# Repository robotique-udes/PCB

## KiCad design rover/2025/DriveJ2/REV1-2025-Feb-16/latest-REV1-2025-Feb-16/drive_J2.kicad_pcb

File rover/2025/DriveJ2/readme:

REV0 - C'est le first draft un peu gros, mais normalement tout est chill

hopefully j'ai le temps de le shrinker un peu avant la commande avec la rev1

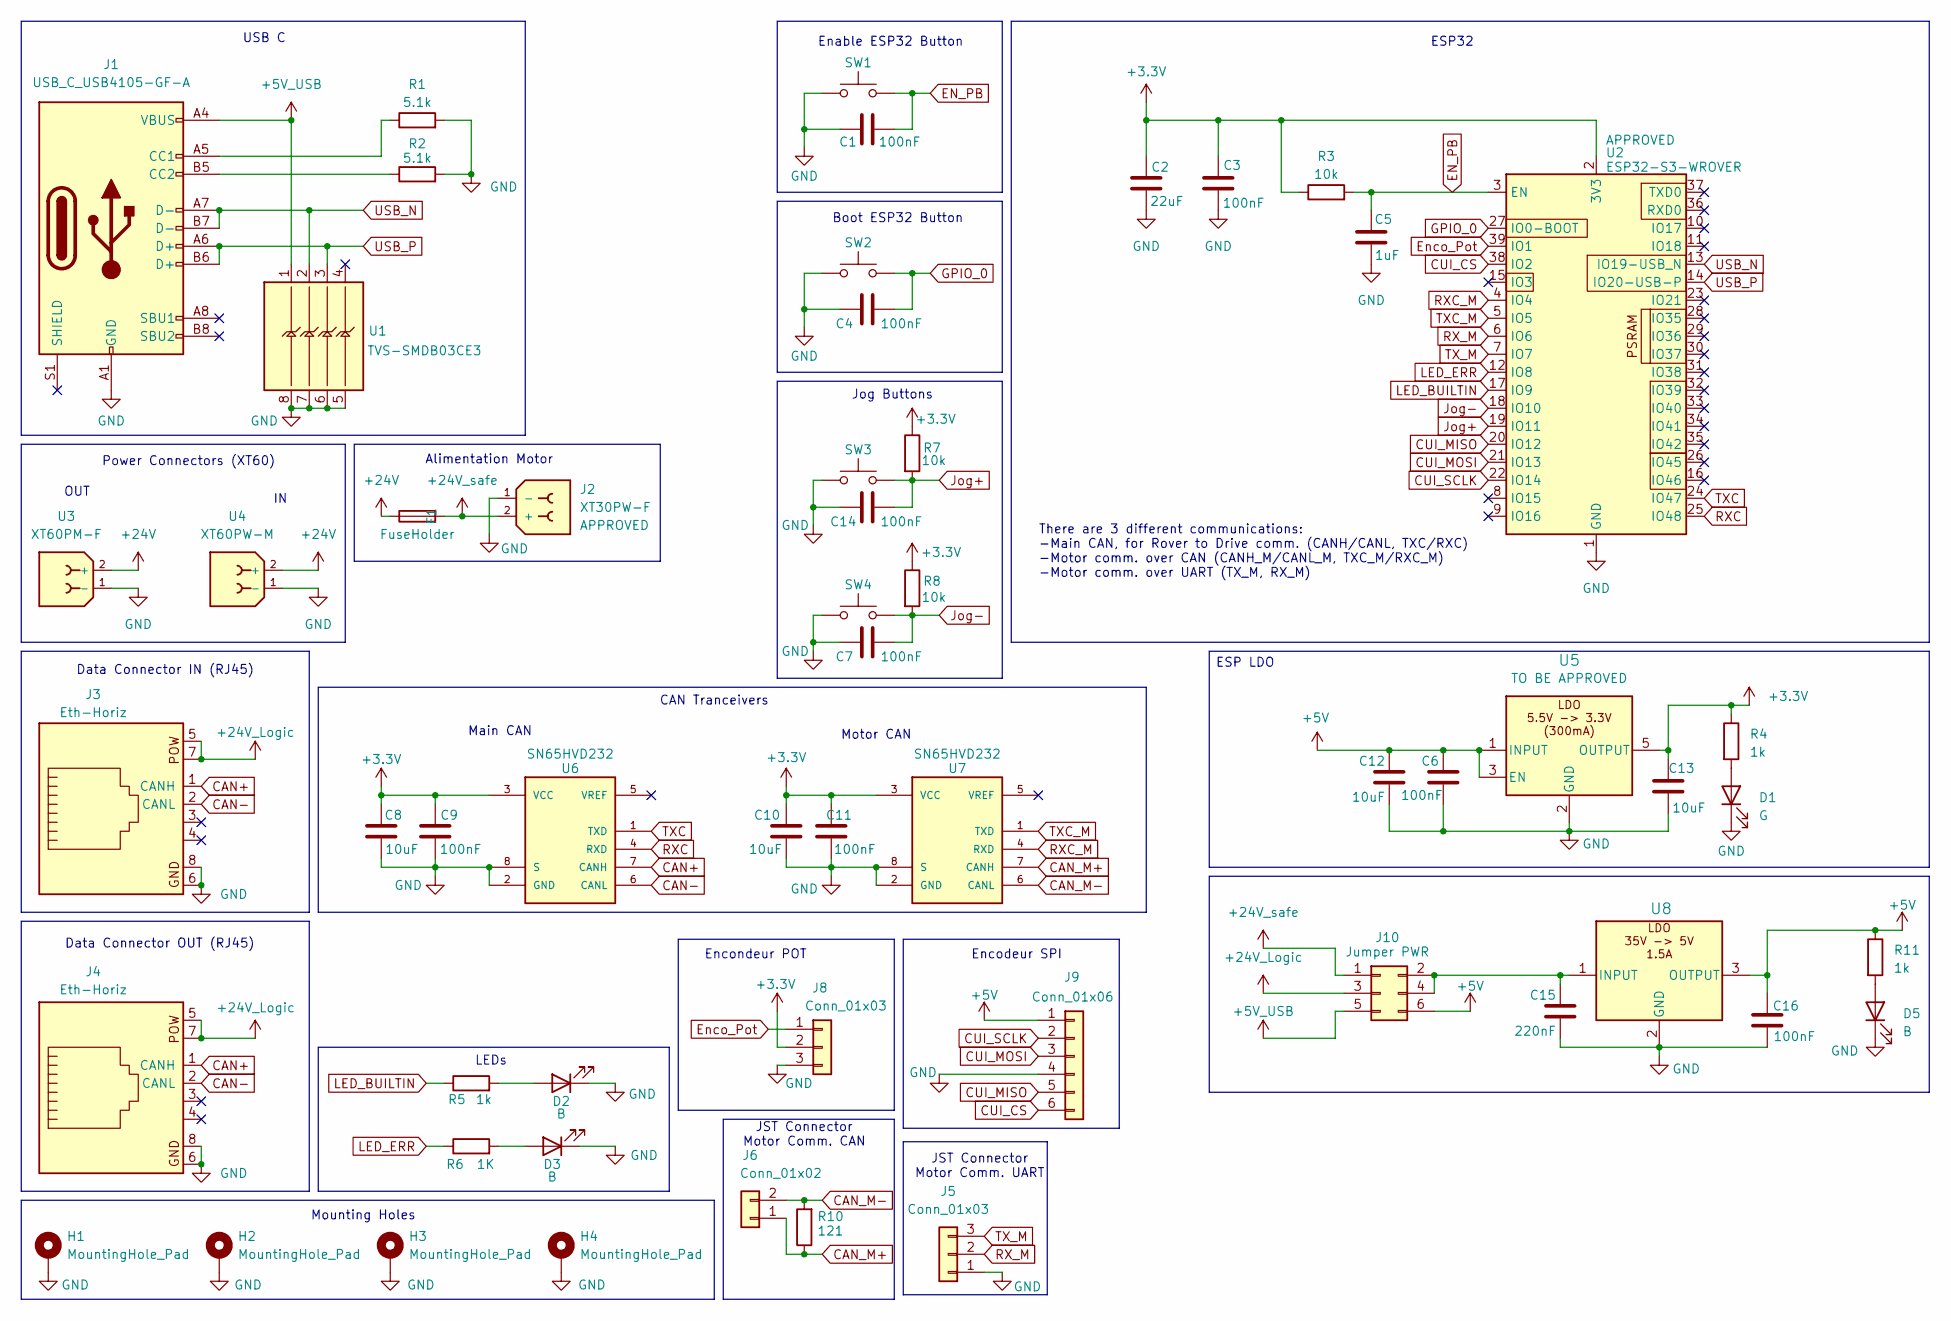
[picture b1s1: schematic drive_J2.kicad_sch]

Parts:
C1, C3, C4, C6, C7, C9, C11, C14, C16: 100nF; C_0805_2012Metric_Pad1.18x1.45mm_HandSolder
C2: 22uF; C_0805_2012Metric_Pad1.18x1.45mm_HandSolder
C5: 1uF; C_0805_2012Metric_Pad1.18x1.45mm_HandSolder
C8, C10, C12, C13: 10uF; C_0805_2012Metric_Pad1.18x1.45mm_HandSolder
C15: 220nF; C_0805_2012Metric_Pad1.18x1.45mm_HandSolder
D1: G; LED_0805_2012Metric_Pad1.15x1.40mm_HandSolder
D2, D3, D5: B; LED_0805_2012Metric_Pad1.15x1.40mm_HandSolder
F1: FuseHolder; FUSE_3568-20
H1, H2, H3, H4: MountingHole_Pad; MountingHole_3.2mm_M3_DIN965_Pad_TopBottom
J1: USB_C_USB4105-GF-A; USB_C_Receptacle_GCT_USB4105-xx-A_16P_TopMnt_Horizontal
J2: XT30PW-F; AMASS_XT30PW-F_1x02_P2.50mm_Horizontal; PARTREV 1.2
J3, J4: Eth-Horiz; Ethernet_Horizontal
J5: Conn_01x03; JST_PH_S3B-PH-K_1x03_P2.00mm_Horizontal
J6: Conn_01x02; JST_PH_S2B-PH-K_1x02_P2.00mm_Horizontal
J8: Conn_01x03; JST_PH_B3B-PH-K_1x03_P2.00mm_Vertical
J9: Conn_01x06; JST_PH_B6B-PH-K_1x06_P2.00mm_Vertical
J10: Jumper PWR; PinHeader_2x03_P2.54mm_Vertical
R1, R2: 5.1k; R_0805_2012Metric_Pad1.20x1.40mm_HandSolder
R3, R7, R8: 10k; R_0805_2012Metric_Pad1.20x1.40mm_HandSolder
R4, R5, R11: 1k; R_0805_2012Metric_Pad1.20x1.40mm_HandSolder
R6: 1K; R_0805_2012Metric_Pad1.20x1.40mm_HandSolder
R10: 121; R_0805_2012Metric_Pad1.20x1.40mm_HandSolder
SW1, SW2, SW3, SW4: SW-PTS815SJM250SMTRLFS; SW-PTS815 SJM250SMTRLFS
U1: TVS-SMDB03CE3; SOIC-8_3.9x4.9mm_P1.27mm
U2: ESP32-S3-WROVER; ESP32-S3-WROOM-1U
U3: XT60PM-F; AMASS_XT60PW-F_1x02_P7.20mm_Horizontal
U4: XT60PW-M; AMASS_XT60PW-M_1x02_P7.20mm_Horizontal
U5: LDO-TLV74033PDBVR; SOT-23-5_HandSoldering
U6, U7: SN65HVD232; SOIC-8_3.9x4.9mm_P1.27mm; PARTREV 4
U8: LDO-LM7805MPX/NOPB; SOT-223-3_TabPin2

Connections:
+3.3V: C2.1, C3.1, C8.1, C9.1, C10.1, C11.1, C13.1, J8.2, R3.1, R4.1, R7.1, R8.1, U2.2 (3V3), U5.5 (OUTPUT), U6.3 (VCC), U7.3 (VCC)
+5V: C6.1, C12.1, C16.1, J9.1, J10.6, R11.1, U5.1 (INPUT), U5.3 (EN), U8.3 (OUTPUT)
+5V_USB: J1.A4 (VBUS), J1.A9 (VBUS), J1.B4 (VBUS), J1.B9 (VBUS), J10.5, U1.1
+24V: F1.2, U3.2 (+), U4.2 (+)
+24V_Logic: J3.5, J3.7, J4.5, J4.7, J10.3
+24V_safe: F1.1, J2.2 (+), J10.1
CAN+: J3.1 (CANH), J4.1 (CANH), U6.7 (CANH)
CAN-: J3.2 (CANL), J4.2 (CANL), U6.6 (CANL)
CAN_M+: J6.1, R10.1, U7.7 (CANH)
CAN_M-: J6.2, R10.2, U7.6 (CANL)
CUI_CS: J9.6, U2.38 (IO2)
CUI_MISO: J9.5, U2.20 (IO12)
CUI_MOSI: J9.3, U2.21 (IO13)
CUI_SCLK: J9.2, U2.22 (IO14)
EN_PB: C1.2, C5.1, R3.2, SW1.4, U2.3 (EN)
Enco_Pot: J8.1, U2.39 (IO1)
GND: C1.1, C2.2, C3.2, C4.1, C5.2, C6.2, C7.1, C8.2, C9.2, C10.2, C11.2, C12.2, C13.2, C14.1, C15.2, C16.2, D1.1 (K), D2.1 (K), D3.1 (K), D5.1 (K), H1.1, H2.1, H3.1, H4.1, J1.A1 (GND), J1.A12 (GND), J1.B1 (GND), J1.B12 (GND), J2.1 (-), J3.6, J3.8, J4.6, J4.8, J5.1, J8.3, J9.4, R1.2, R2.2, SW1.1, SW1.2, SW2.1, SW2.2, SW3.1, SW3.2, SW4.1, SW4.2, U1.5, U1.6, U1.7, U1.8, U2.1 (GND), U2.40 (GND), U2.41 (GND), U3.1 (-), U4.1 (-), U5.2 (GND), U6.2 (GND), U6.8 (S), U7.2 (GND), U7.8 (S), U8.2 (GND)
GPIO_0: C4.2, SW2.4, U2.27 (IO0-BOOT)
Jog+: C14.2, R7.2, SW3.4, U2.19 (IO11)
Jog-: C7.2, R8.2, SW4.4, U2.18 (IO10)
LED_BUILTIN: R5.1, U2.17 (IO9)
LED_ERR: R6.1, U2.12 (IO8)
unnamed: D1.2 (A), R4.2
unnamed: D2.2 (A), R5.2
unnamed: D3.2 (A), R6.2
unnamed: D5.2 (A), R11.2
unnamed: J1.A5 (CC1), R1.1
unnamed: J1.B5 (CC2), R2.1
unnamed: C15.1, J10.2, J10.4, U8.1 (INPUT)
RXC: U2.25 (IO48), U6.4 (RXD)
RXC_M: U2.4 (IO4), U7.4 (RXD)
RX_M: J5.2, U2.6 (IO6)
TXC: U2.24 (IO47), U6.1 (TXD)
TXC_M: U2.5 (IO5), U7.1 (TXD)
TX_M: J5.3, U2.7 (IO7)
USB_N: J1.A7 (D-), J1.B7 (D-), U1.2, U2.13 (IO19-USB_N)
USB_P: J1.A6 (D+), J1.B6 (D+), U1.3, U2.14 (IO20-USB-P)

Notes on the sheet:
ESP32
Data Connector IN (RJ45)
OUT
Mounting Holes
Encodeur SPI
Power Connectors (XT60)
JST Connector Motor Comm. UART
Main CAN
Motor CAN
There are 3 different communications: -Main CAN, for Rover to Drive comm. (CANH/CANL, TXC/RXC) -Motor comm. over CAN (CANH_M/CANL_M, TXC_M/RXC_M) -Motor comm. over UART (TX_M, RX_M)
ESP LDO
Alimentation Motor
Boot ESP32 Button
Jog Buttons
Enable ESP32 Button
CAN Tranceivers
Data Connector OUT (RJ45)
USB C
LEDs
Encondeur POT
JST Connector Motor Comm. CAN

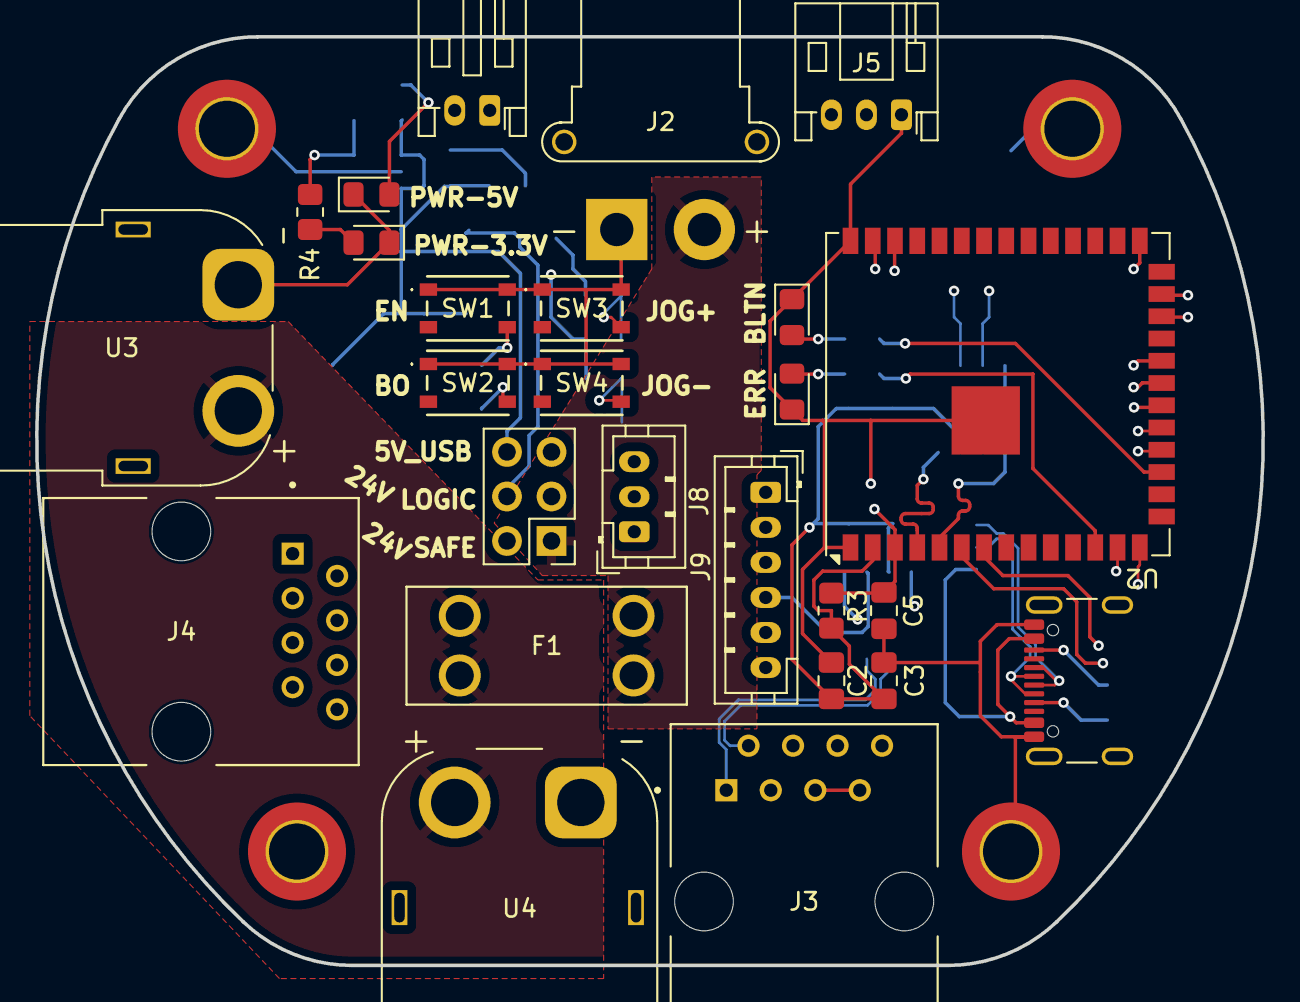
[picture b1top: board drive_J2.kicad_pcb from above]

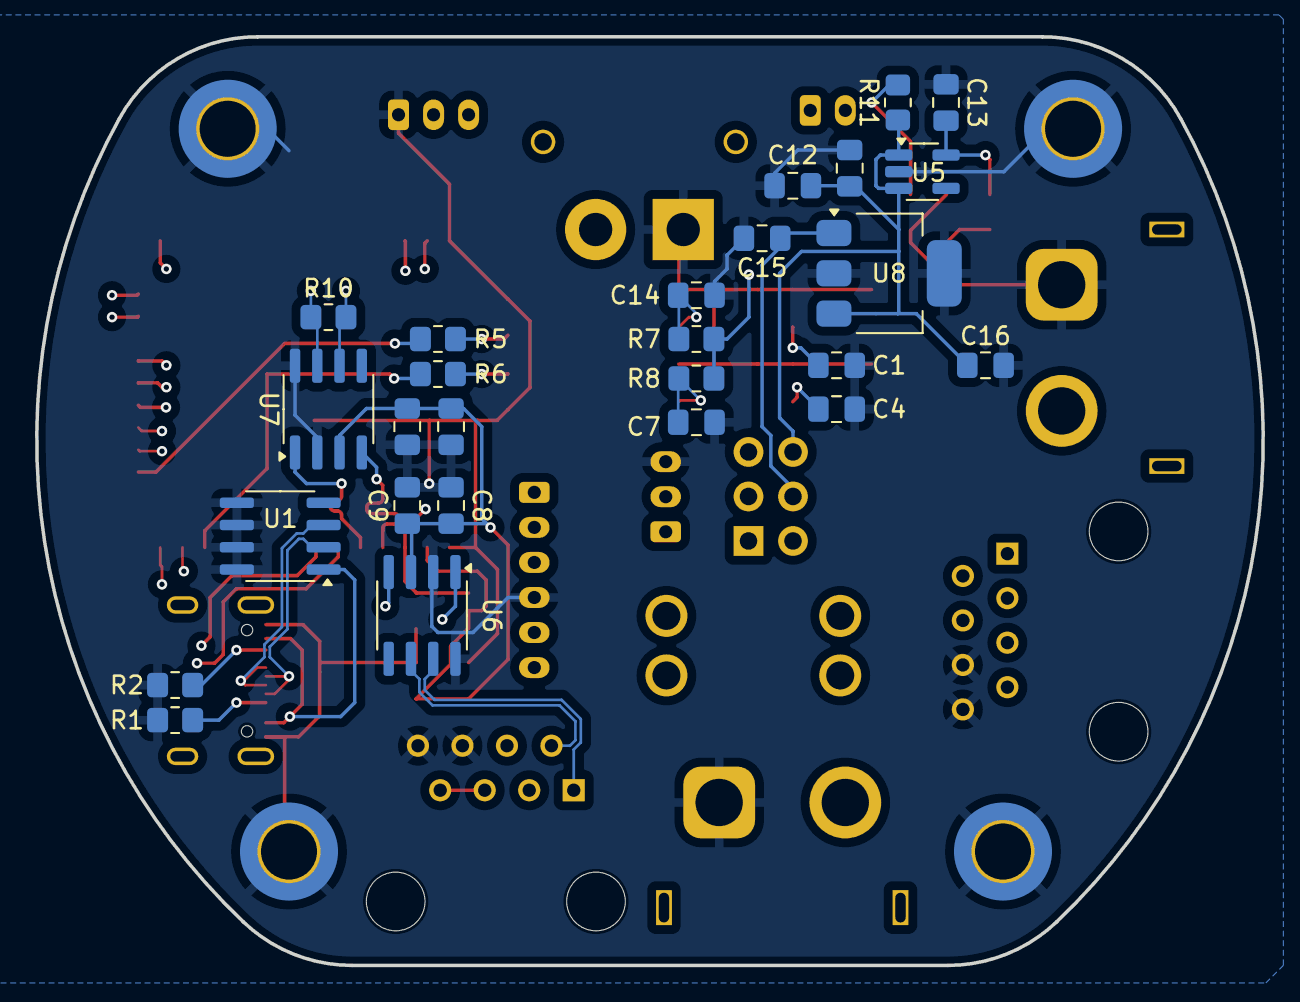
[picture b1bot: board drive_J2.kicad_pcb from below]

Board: 4 copper layers, 70.0 x 53.0 mm, 56 parts (26 on the bottom side), 37 nets.

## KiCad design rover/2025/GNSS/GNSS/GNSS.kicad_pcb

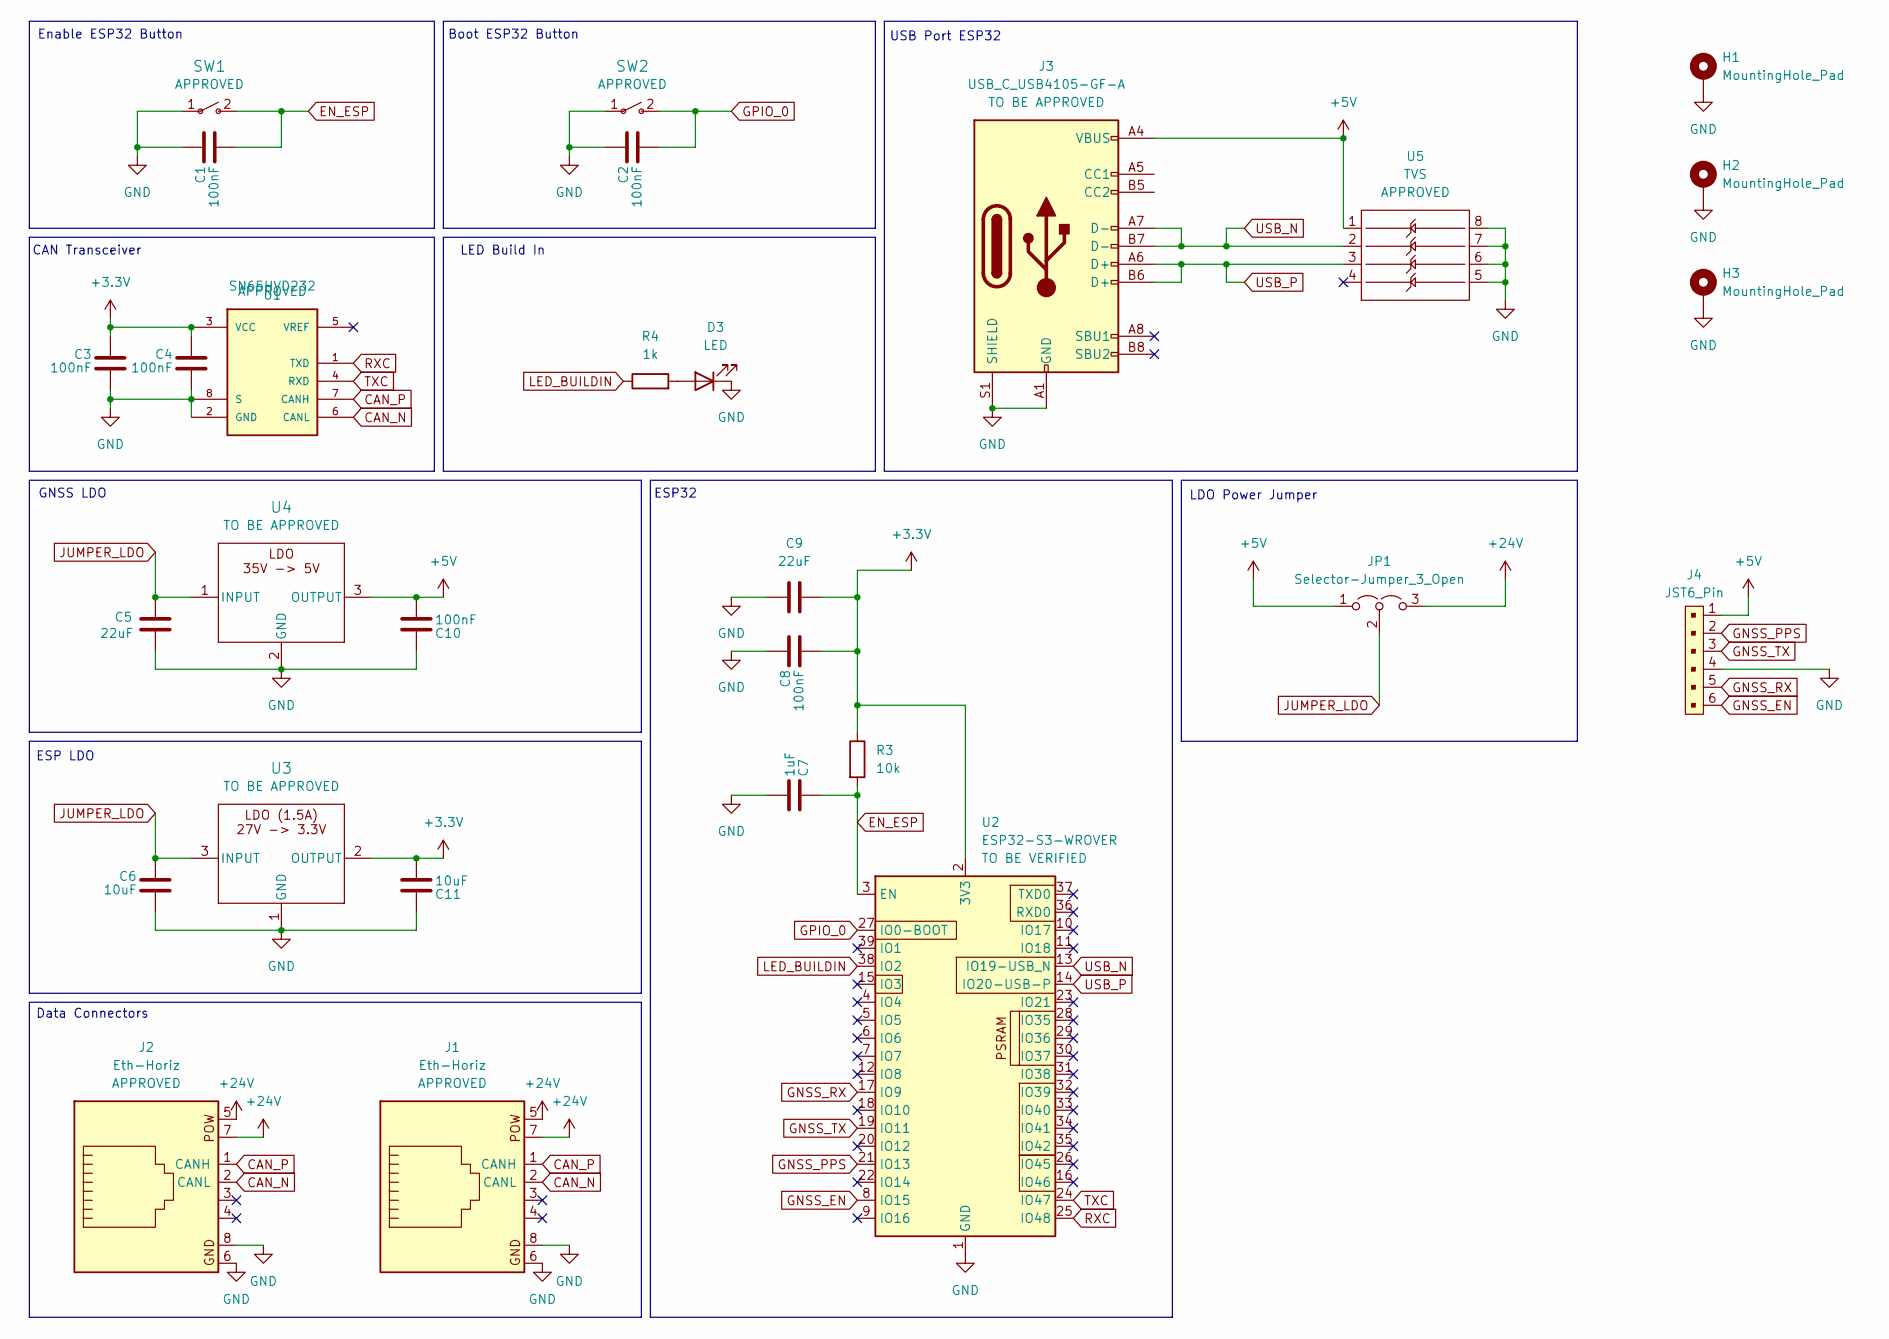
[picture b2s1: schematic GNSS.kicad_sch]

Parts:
C1, C2, C3, C4, C8, C10: 100nF; C_0805_2012Metric_Pad1.18x1.45mm_HandSolder
C5, C9: 22uF; C_0805_2012Metric_Pad1.18x1.45mm_HandSolder
C6, C11: 10uF; C_0805_2012Metric_Pad1.18x1.45mm_HandSolder
C7: 1uF; C_0805_2012Metric_Pad1.18x1.45mm_HandSolder
D3: LED; LED_0805_2012Metric_Pad1.15x1.40mm_HandSolder
H1, H2, H3: MountingHole_Pad; MountingHole_3.2mm_M3_DIN965_Pad_TopBottom
J1, J2: Eth-Horiz; Ethernet_Horizontal
J3: USB_C_USB4105-GF-A; USB_C_Receptacle_GCT_USB4105-xx-A_16P_TopMnt_Horizontal
J4: JST6_Pin; JST_XH_B6B-XH-AM_1x06_P2.50mm_Vertical
JP1: Selector-Jumper_3_Open; PinHeader_1x03_P2.54mm_Vertical
R3: 10k; R_0805_2012Metric_Pad1.20x1.40mm_HandSolder
R4: 1k; R_0805_2012Metric_Pad1.20x1.40mm_HandSolder
SW1, SW2: TS09-63-25-WT-160-SMT-TR; SW_DIP_SPSTx01_Slide_6.7x4.1mm_W8.61mm_P2.54mm_LowProfile
U1: SN65HVD232; SOIC-8_3.9x4.9mm_P1.27mm; PARTREV 4
U2: ESP32-S3-WROVER; ESP32-S3-WROOM-1U
U3: LD1086DT33TR; TO-252-2
U4: LDO-LM7805MPX/NOPB; SOT-223-3_TabPin2
U5: TVS; SOIC-8_3.9x4.9mm_P1.27mm

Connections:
+3.3V: C3.1, C4.1, C8.2, C9.2, C11.2, R3.1, U1.3 (VCC), U2.2 (3V3), U3.2 (OUTPUT)
+5V: C10.2, J3.A4 (VBUS), J3.A9 (VBUS), J3.B4 (VBUS), J3.B9 (VBUS), J4.1, JP1.1 (A), U4.3 (OUTPUT), U5.1
+24V: J1.5, J1.7, J2.5, J2.7, JP1.3 (B)
CAN_N: J1.2 (CANL), J2.2 (CANL), U1.6 (CANL)
CAN_P: J1.1 (CANH), J2.1 (CANH), U1.7 (CANH)
EN_ESP: C1.2, C7.1, R3.2, SW1.2, U2.3 (EN)
GND: C1.1, C2.1, C3.2, C4.2, C5.1, C6.2, C7.2, C8.1, C9.1, C10.1, C11.1, D3.1 (K), H1.1, H2.1, H3.1, J1.6, J1.8, J2.6, J2.8, J3.A1 (GND), J3.A12 (GND), J3.B1 (GND), J3.B12 (GND), J3.S1 (SHIELD), J4.4, SW1.1, SW2.1, U1.2 (GND), U1.8 (S), U2.1 (GND), U2.40 (GND), U2.41 (GND), U3.1 (GND), U4.2 (GND), U5.5, U5.6, U5.7, U5.8
GNSS_EN: J4.6, U2.8 (IO15)
GNSS_PPS: J4.2, U2.21 (IO13)
GNSS_RX: J4.5, U2.17 (IO9)
GNSS_TX: J4.3, U2.19 (IO11)
GPIO_0: C2.2, SW2.2, U2.27 (IO0-BOOT)
JUMPER_LDO: C5.2, C6.1, JP1.2 (C), U3.3 (INPUT), U4.1 (INPUT)
LED_BUILDIN: R4.1, U2.38 (IO2)
unnamed: D3.2 (A), R4.2
RXC: U1.1 (TXD), U2.25 (IO48)
TXC: U1.4 (RXD), U2.24 (IO47)
USB_N: J3.A7 (D-), J3.B7 (D-), U2.13 (IO19-USB_N), U5.2
USB_P: J3.A6 (D+), J3.B6 (D+), U2.14 (IO20-USB-P), U5.3

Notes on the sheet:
Enable ESP32 Button
Data Connectors
Boot ESP32 Button
LED Build In
ESP32
CAN Transceiver
ESP LDO
GNSS LDO
LDO Power Jumper
USB Port ESP32

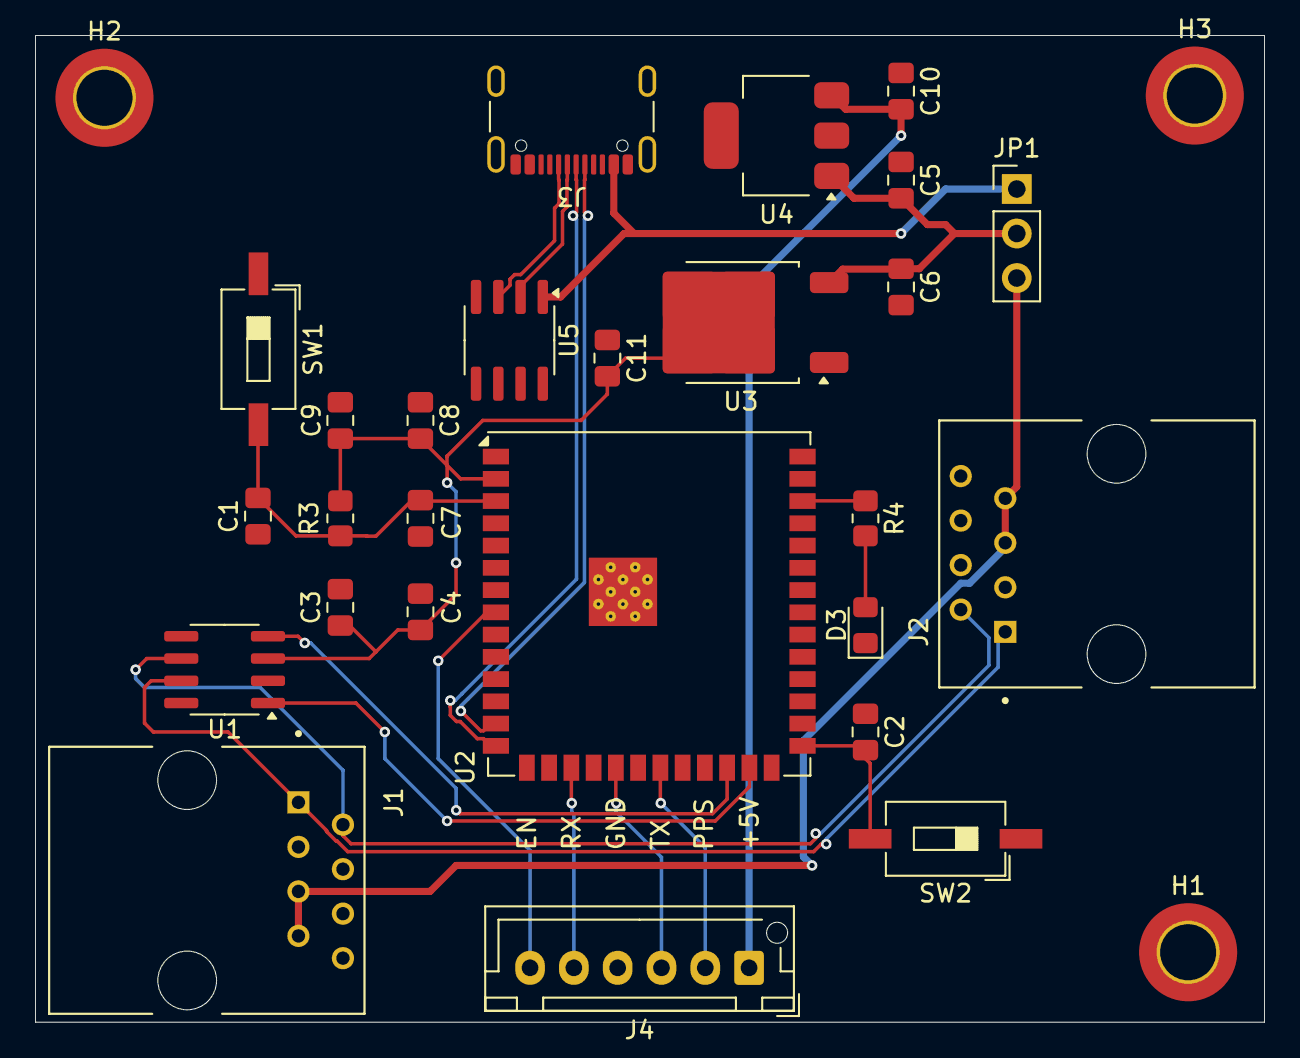
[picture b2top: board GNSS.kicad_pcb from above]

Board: 2 copper layers, 70.1 x 56.3 mm, 29 parts (0 on the bottom side), 19 nets.

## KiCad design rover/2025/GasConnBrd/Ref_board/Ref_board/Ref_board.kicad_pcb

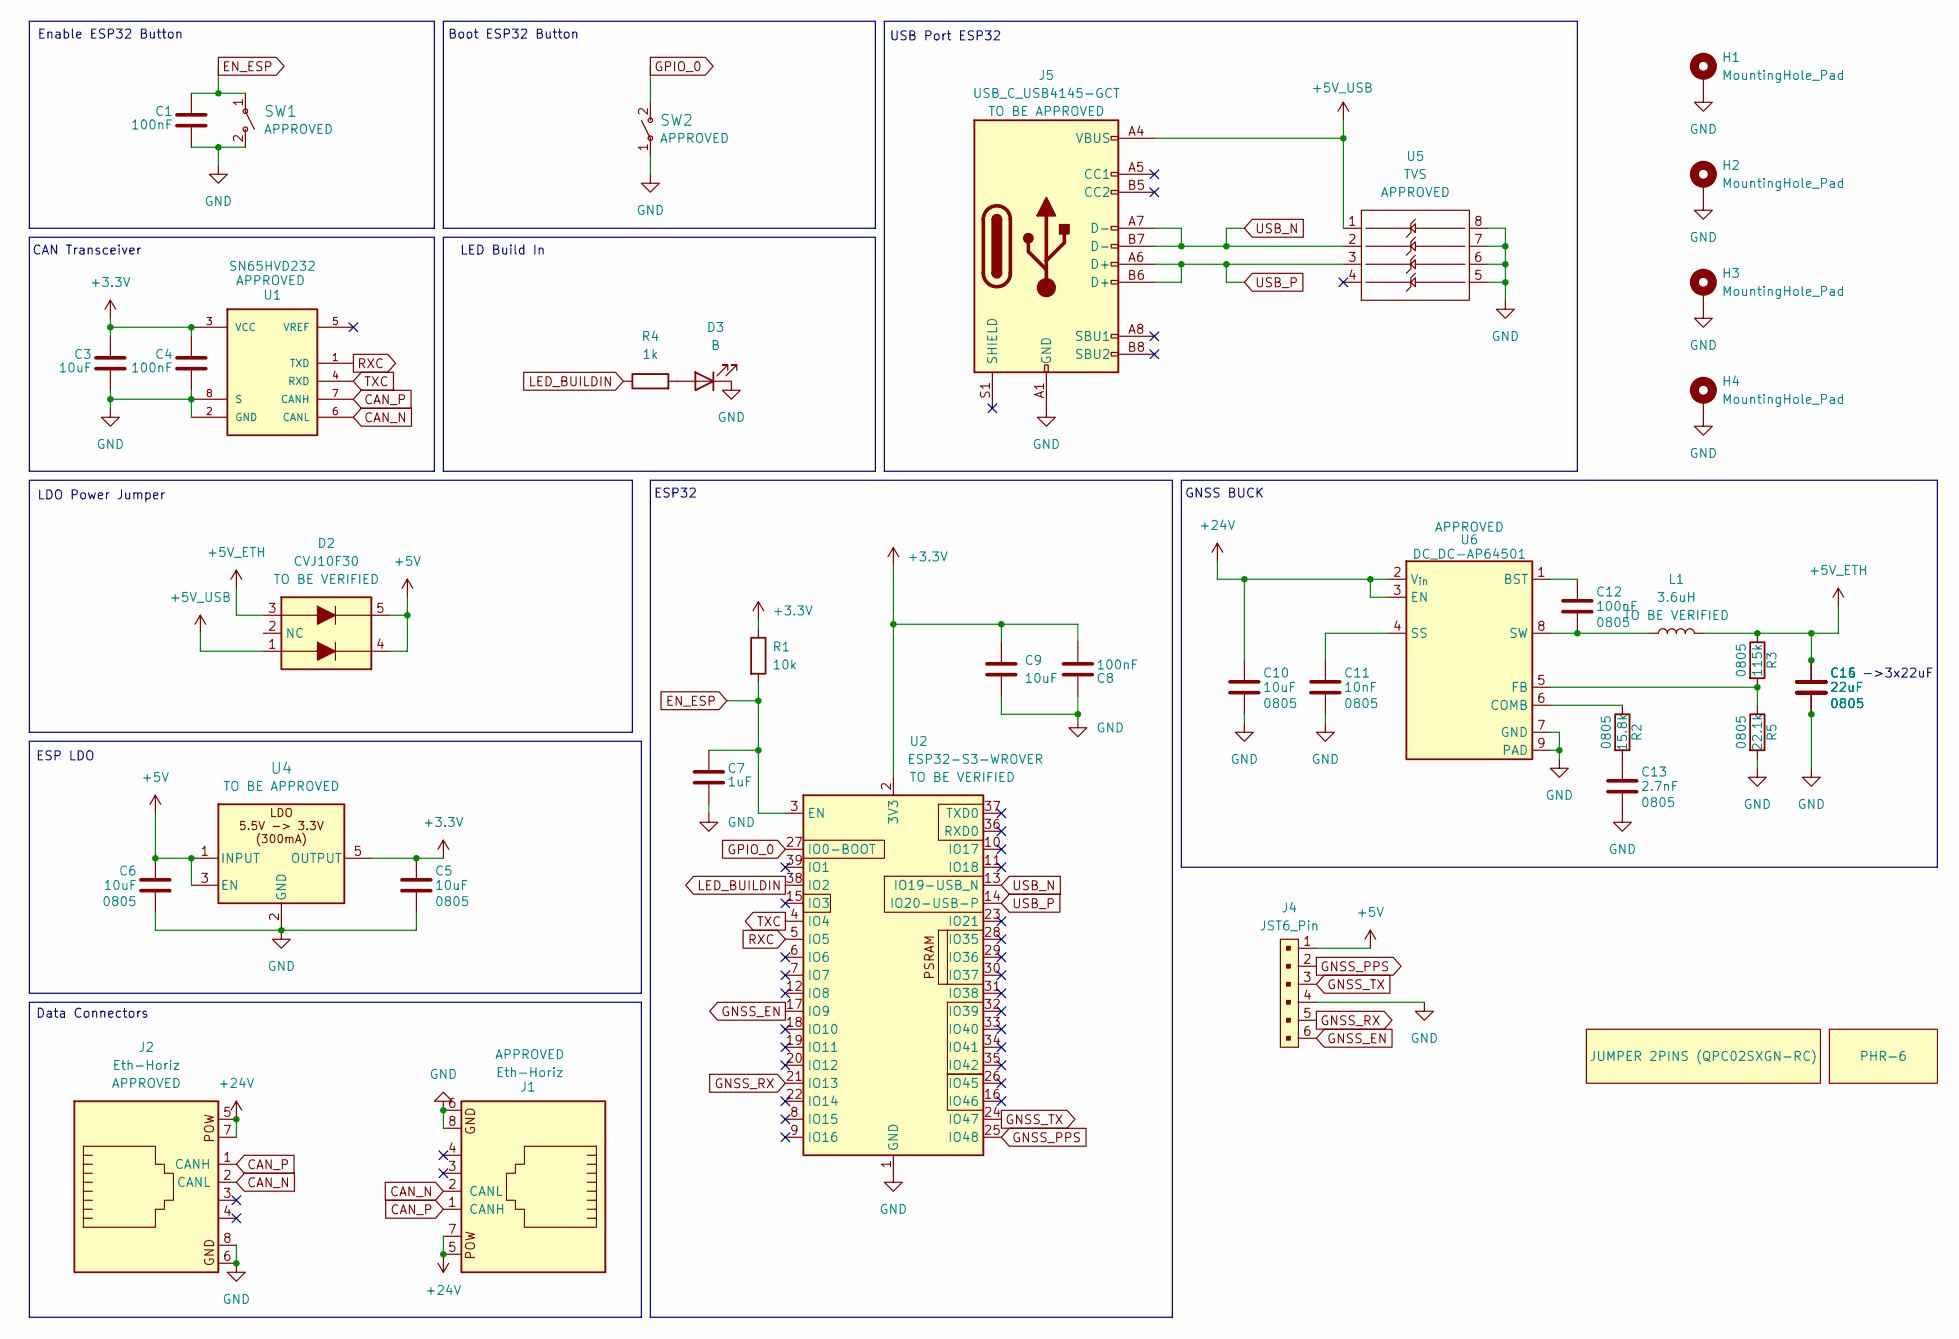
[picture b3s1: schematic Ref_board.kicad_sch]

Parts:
C1, C4, C8, C12: 100nF; C_0805_2012Metric_Pad1.18x1.45mm_HandSolder
C3, C5, C6, C9, C10: 10uF; C_0805_2012Metric_Pad1.18x1.45mm_HandSolder
C7: 1uF; C_0805_2012Metric_Pad1.18x1.45mm_HandSolder
C11: 10nF; C_0805_2012Metric_Pad1.18x1.45mm_HandSolder
C13: 2.7nF; C_0805_2012Metric_Pad1.18x1.45mm_HandSolder
C14, C15, C16: 22uF; C_0805_2012Metric_Pad1.18x1.45mm_HandSolder
D2: CVJ10F30; Diode_schottky-CVJ10F30
D3: B; LED_0805_2012Metric_Pad1.15x1.40mm_HandSolder
G1: PHR-6
G2: JUMPER 2PINS (QPC02SXGN-RC)
H1, H2, H3, H4: MountingHole_Pad; MountingHole_3.2mm_M3_DIN965_Pad_TopBottom
J1, J2: Eth-Horiz; Ethernet_Horizontal
J4: JST6_Pin; JST_PH_B6B-PH-K_1x06_P2.00mm_Vertical
J5: USB_C_USB4145-GCT; USB4145_GCT
L1: 3.6uH; L_3.6u_ASPI-6045S-3R6N-T
R1: 10k; R_0805_2012Metric_Pad1.20x1.40mm_HandSolder
R2: 15.8k; R_0805_2012Metric_Pad1.20x1.40mm_HandSolder
R3: 115k; R_0805_2012Metric_Pad1.20x1.40mm_HandSolder
R4: 1k; R_0805_2012Metric_Pad1.20x1.40mm_HandSolder
R5: 22.1k; R_0805_2012Metric_Pad1.20x1.40mm_HandSolder
SW1, SW2: TS09-63-25-WT-160-SMT-TR; SW_DIP_SPSTx01_Slide_6.7x4.1mm_W8.61mm_P2.54mm_LowProfile
U1: SN65HVD232; SOIC-8_3.9x4.9mm_P1.27mm; PARTREV 4
U2: ESP32-S3-WROVER; ESP32-S3-WROOM-1U
U4: LDO-TLV74033PDBVR; SOT-23-5_HandSoldering
U5: TVS; SOIC-8_3.9x4.9mm_P1.27mm
U6: DC_DC-AP64501; SOIC-8-1EP_3.9x4.9mm_P1.27mm_EP2.29x3mm

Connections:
+3.3V: C3.1, C4.1, C5.1, C8.2, C9.1, R1.1, U1.3 (VCC), U2.2 (3V3), U4.5 (OUTPUT)
+5V: C6.1, D2.4, D2.5, J4.1, U4.1 (INPUT), U4.3 (EN)
+5V_ETH: C14.1, C15.1, C16.1, D2.3, L1.2, R3.1
+5V_USB: D2.1, J5.A4 (VBUS), J5.A9 (VBUS), J5.B4 (VBUS), J5.B9 (VBUS), U5.1
+24V: C10.1, J1.5, J1.7, J2.5, J2.7, U6.2 (V_{in}), U6.3 (EN)
CAN_N: J1.2 (CANL), J2.2 (CANL), U1.6 (CANL)
CAN_P: J1.1 (CANH), J2.1 (CANH), U1.7 (CANH)
EN_ESP: C1.1, C7.1, R1.2, SW1.1, U2.3 (EN)
GND: C1.2, C3.2, C4.2, C5.2, C6.2, C7.2, C8.1, C9.2, C10.2, C11.2, C13.2, C14.2, C15.2, C16.2, D3.1 (K), H1.1, H2.1, H3.1, H4.1, J1.6, J1.8, J2.6, J2.8, J4.4, J5.A1 (GND), J5.A12 (GND), J5.B1 (GND), J5.B12 (GND), R5.2, SW1.2, SW2.1, U1.2 (GND), U1.8 (S), U2.1 (GND), U2.40 (GND), U2.41 (GND), U4.2 (GND), U5.5, U5.6, U5.7, U5.8, U6.7 (GND), U6.9 (PAD)
GNSS_EN: J4.6, U2.17 (IO9)
GNSS_PPS: J4.2, U2.25 (IO48)
GNSS_RX: J4.5, U2.21 (IO13)
GNSS_TX: J4.3, U2.24 (IO47)
GPIO_0: SW2.2, U2.27 (IO0-BOOT)
LED_BUILDIN: R4.1, U2.38 (IO2)
unnamed: C13.1, R2.2
unnamed: D3.2 (A), R4.2
unnamed: C12.1, U6.1 (BST)
unnamed: R2.1, U6.6 (COMB)
unnamed: R3.2, R5.1, U6.5 (FB)
unnamed: C11.1, U6.4 (SS)
unnamed: C12.2, L1.1, U6.8 (SW)
RXC: U1.1 (TXD), U2.5 (IO5)
TXC: U1.4 (RXD), U2.4 (IO4)
USB_N: J5.A7 (D-), J5.B7 (D-), U2.13 (IO19-USB_N), U5.2
USB_P: J5.A6 (D+), J5.B6 (D+), U2.14 (IO20-USB-P), U5.3

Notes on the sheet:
Enable ESP32 Button
->3x22uF
Data Connectors
Boot ESP32 Button
LED Build In
ESP32
CAN Transceiver
ESP LDO
GNSS BUCK
LDO Power Jumper
USB Port ESP32

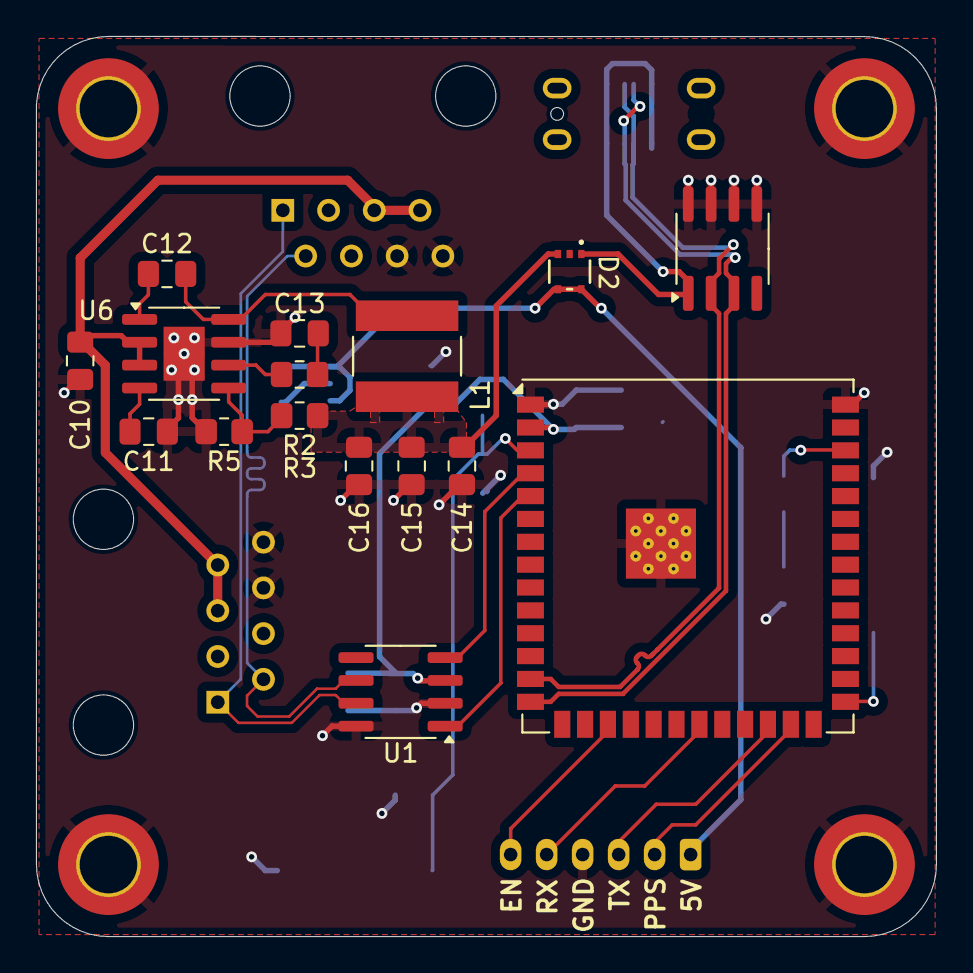
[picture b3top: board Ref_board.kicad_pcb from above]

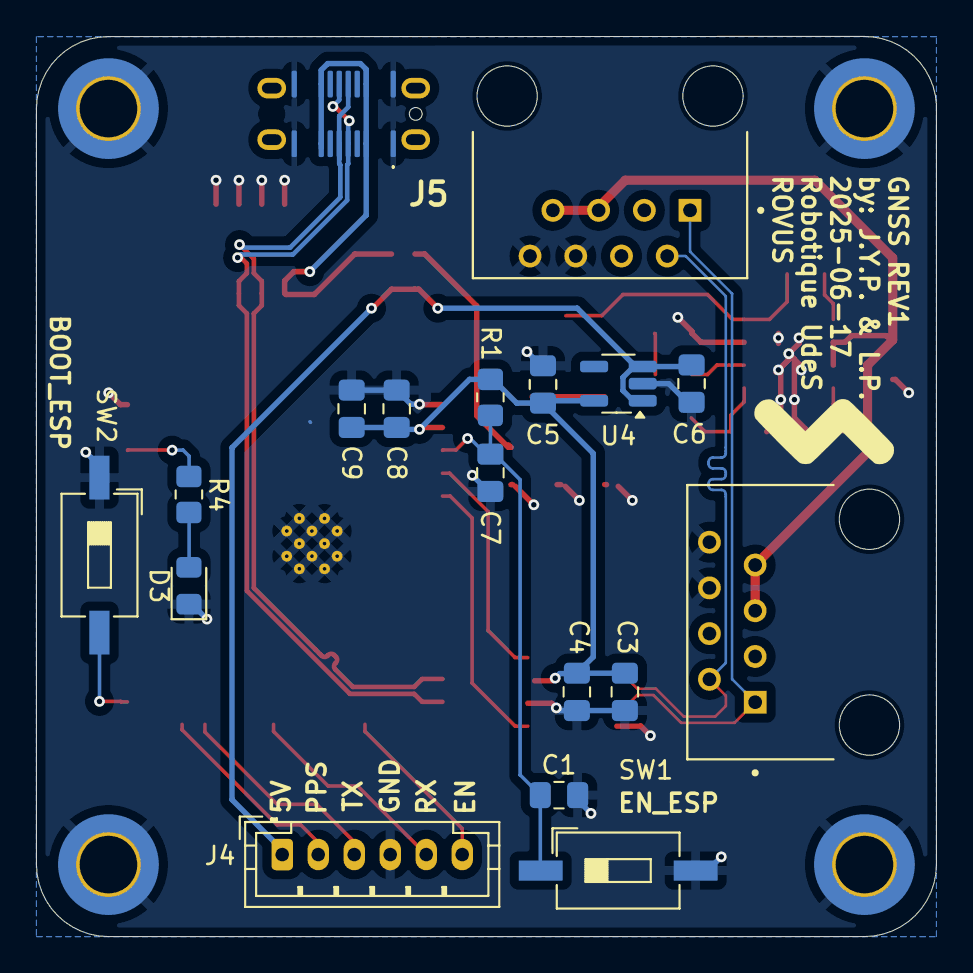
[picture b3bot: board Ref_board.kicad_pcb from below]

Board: 4 copper layers, 50.0 x 50.0 mm, 38 parts (18 on the bottom side), 26 nets.

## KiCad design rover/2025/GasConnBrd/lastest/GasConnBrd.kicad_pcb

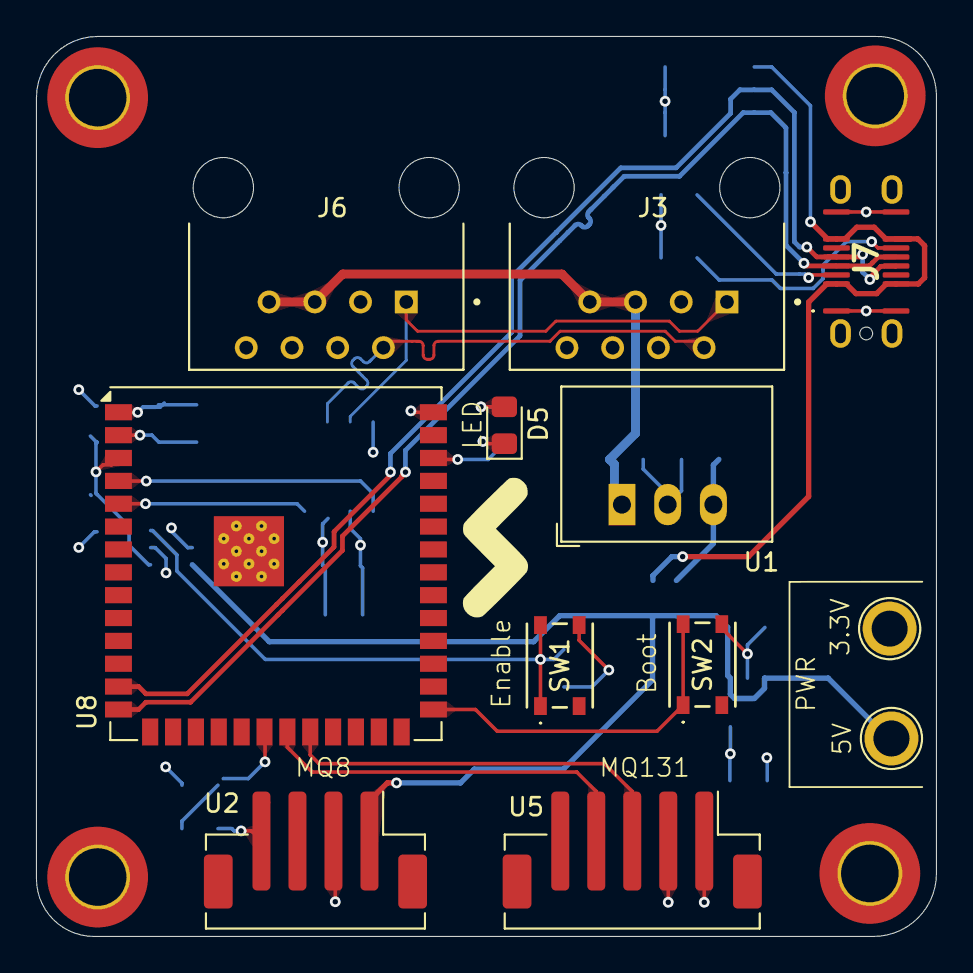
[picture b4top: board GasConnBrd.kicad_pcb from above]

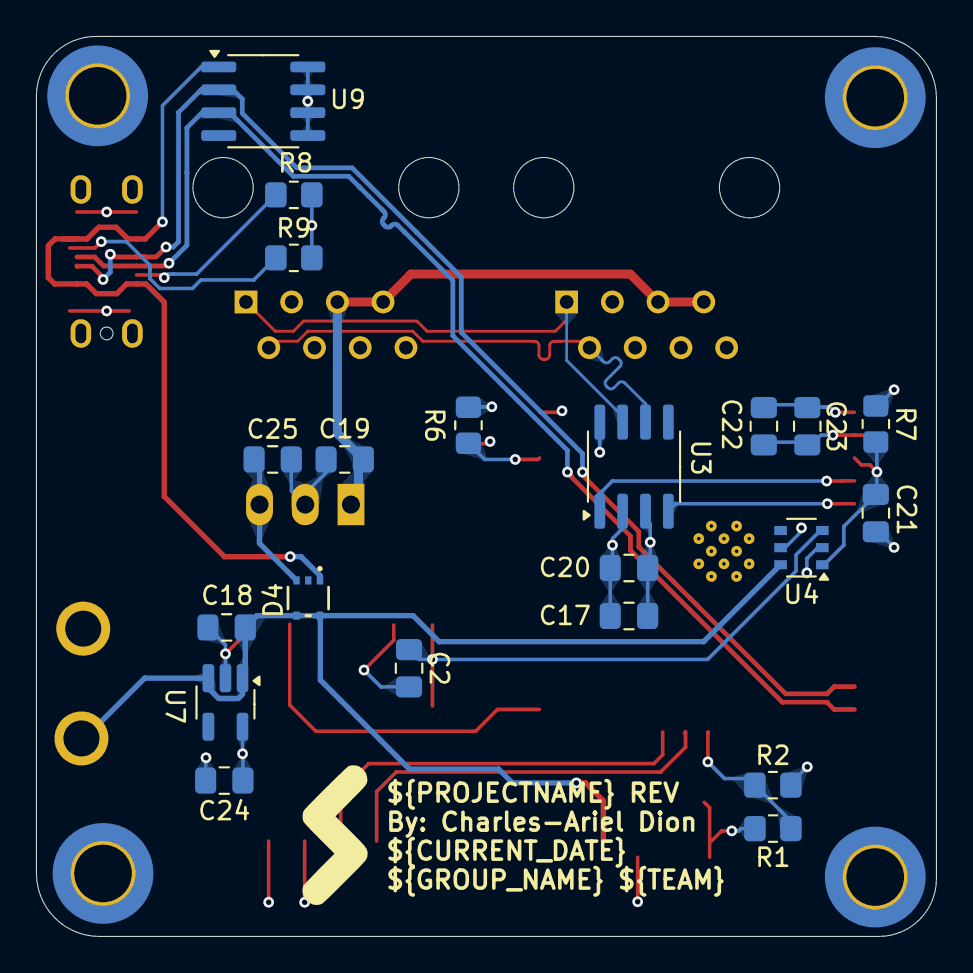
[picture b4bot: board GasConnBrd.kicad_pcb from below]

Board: 4 copper layers, 50.0 x 50.0 mm, 37 parts (21 on the bottom side), 23 nets.

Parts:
C2, C20, C23: 100nF; C_0805_2012Metric_Pad1.18x1.45mm_HandSolder
C17, C18, C19, C22, C24, C25: 10uF; C_0805_2012Metric_Pad1.18x1.45mm_HandSolder
C21: 1uF; C_0805_2012Metric_Pad1.18x1.45mm_HandSolder
D4: CVJ10F30; Diode_schottky-CVJ10F30
D5: B; LED_0805_2012Metric_Pad1.15x1.40mm_HandSolder
H9, H10, H11, H12: MountingHole_Pad; MountingHole
J3, J6: Eth-Horiz; Ethernet_Horizontal
J7: USB_C_USB4145-GCT; USB4145_GCT
R1, R7: 10k; R_0805_2012Metric_Pad1.20x1.40mm_HandSolder
R2: 20k; R_0805_2012Metric_Pad1.20x1.40mm_HandSolder
R6: 1k; R_0805_2012Metric_Pad1.20x1.40mm_HandSolder
R8, R9: 5k1; R_0805_2012Metric_Pad1.20x1.40mm_HandSolder
SW1, SW2: SW-PTS815SJM250SMTRLFS; SW-PTS815 SJM250SMTRLFS
TP1, TP2: TestPoint; TestPoint_Plated_Hole_D2.0mm
U1: R-78E5.0-0.5; Converter_DCDC_RECOM_R-78E-0.5_THT
U2: MQ-8; JST_PH_B4B-PH-SM4-TB_1x04-1MP_P2.00mm_Vertical
U3: SN65HVD232; SOIC-8_3.9x4.9mm_P1.27mm
U4: Volt_check-NCV308; TSOP-6_1.65x3.05mm_P0.95mm
U5: MQ-131; JST_PH_B5B-PH-SM4-TB_1x05-1MP_P2.00mm_Vertical
U7: LDO-TLV74033PDBVR; SOT-23-5_HandSoldering
U8: ESP32-S3-WROVER; ESP32-S3-WROOM-1U
U9: TVS; SOIC-8_3.9x4.9mm_P1.27mm

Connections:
+3.3V: C17.1, C20.1, C22.1, C23.2, C24.1, R7.1, TP2.1, U3.3 (VCC), U4.5 (SENSE), U5.1 (3.3V), U7.5 (OUTPUT), U8.2 (3V3)
+5V: C18.1, D4.4, D4.5, TP1.1, U2.1 (5V), U4.6 (VDD), U7.1 (INPUT), U7.3 (EN)
+5V_ETH: C25.1, D4.3, U1.3 (OUT)
+5V_USB: D4.1, J7.A4 (VBUS), J7.A9 (VBUS), J7.B4 (VBUS), J7.B9 (VBUS), U9.1
+24V: C19.1, J3.5, J3.7, J6.5, J6.7, U1.1 (IN)
/Sensors/MQ8_AOUT_5V: R1.1 (+), U2.4 (A0)
CAN_N: J3.2 (CANL), J6.2 (CANL), U3.6 (CANL)
CAN_P: J3.1 (CANH), J6.1 (CANH), U3.7 (CANH)
EN_ESP: C21.1, R7.2, U4.1 (RESET), U8.3 (EN)
EN_SW: C2.1, SW1.1, SW1.2, U4.3 (MR)
GND: C2.2, C17.2, C18.2, C19.2, C20.2, C21.2, C22.2, C23.1, C24.2, C25.2, D5.1 (K), H9.1, H10.1, H11.1, H12.1, J3.6, J3.8, J6.6, J6.8, J7.A1 (GND), J7.A12 (GND), J7.B1 (GND), J7.B12 (GND), J7.S1 (SHIELD), R2.2 (-), R8.2, R9.1, SW1.4, SW2.4, U1.2 (GND), U2.2 (GND), U3.2 (GND), U3.8 (S), U4.2 (GND), U5.2 (GND), U7.2 (GND), U8.1 (GND), U8.40 (GND), U8.41 (GND), U9.5, U9.6, U9.7, U9.8
GPIO_0: SW2.1, SW2.2, U8.27 (IO0-BOOT)
LED_BUILDIN: R6.1, U8.38 (IO2)
MQ8_AOUT: R1.2 (-), R2.1 (+), U8.20 (IO12)
MQ131_SCL: U5.4 (SCL), U8.21 (IO13)
MQ131_SDA: U5.3 (SDA), U8.22 (IO14)
unnamed: D5.2 (A), R6.2
unnamed: J7.A5 (CC1), R8.1
unnamed: J7.B5 (CC2), R9.2
RXC: U3.1 (TXD), U8.4 (IO4)
TXC: U3.4 (RXD), U8.5 (IO5)
USB_N: J7.A7 (D-), J7.B7 (D-), U8.13 (IO19-USB_N), U9.2
USB_P: J7.A6 (D+), J7.B6 (D+), U8.14 (IO20-USB-P), U9.3
